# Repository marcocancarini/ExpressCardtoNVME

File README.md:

# ExpressCard → M.2 NVMe for the ThinkPad X230

An adapter that lets you use an **M.2 NVMe 2230 or 2242** SSD (M-key or B+M-key) in the **ExpressCard/54** slot
of a ThinkPad X230 (and in general in any ExpressCard slot with PCIe). It is a bare board, with no shell, that slides
straight into the slot. It is 70 mm long, like "short" ExpressCards: it sits flush with the slot instead of sticking out.

> **Status:** design complete and DRC-clean, **not yet manufactured or tested on hardware**.
> Before ordering, follow the *Checks before ordering* section of the [guide](GUIDE.md).

## Variants

| Variant | Form factor | USB | Notes |
|---|---|---|---|
| `EC2M2_34` | ExpressCard/34 (34 × 70 mm) | no | fits /34 and /54 slots |
| `EC2M2_34_USB5V` | ExpressCard/34 | yes, 5 V | USB pads on the left side, next to the M.2 |
| `EC2M2_54` | ExpressCard/54 (L-shaped, 54 × 70 mm) | no | more stable in a /54 slot |
| `EC2M2_54_USB5V` | ExpressCard/54 | yes, 5 V | USB pads + cut-out to house a small USB receiver |

| 34 mm | 34 mm + USB | 54 mm | 54 mm + USB |
|---|---|---|---|
|  |  |  |  |

The renders show the bare board only (outline, copper, silkscreen): the components have no 3D models here.

## Features

- **PCIe x1** from the ExpressCard slot to the M.2 connector (M-key, low-profile 2.3 mm: **single-sided SSDs only**); differential pairs at **~86 Ω**
  (computed with an included 2D field solver, `gen/impedance.py`).
- **Screw mounting** for the SSD (**single-sided only**): two M2 SMT nuts (H 1.0 mm) on the bottom side at the 2230 and 2242
  positions (hand-soldered, optional: without them the SSD is held with kapton tape).
- SSD **activity LED** and an optional **CLKREQ#→GND jumper** for SSDs that are not detected.
- **USB versions:** the slot's USB 2.0 port is brought out to pads, with a **3.3 → 5 V boost** (TPS61240, 200 mA guaranteed)
  because the ExpressCard slot does not provide 5 V. The power block sits in the free strip to the left of the SSD. A **separate 3.3 V pad** (3V3) is for 3.3 V devices
  or measurements; it is placed away from the 5V pad so the two cannot be confused.
- 2 layers, **0.6 mm** thick (required by the ExpressCard connector), JLCPCB-compatible rules; BOM with LCSC part numbers and assembly-ready files.
- ExpressCard connector footprint and board outline (arms into the connector rails) taken from the FCI **10030570** drawing (rev M).
- On the back: a small **QR code** linking to this repository.
- **3D-printable case** for transport and storage (see below).

## Printable case

In the slot the board must be used **bare**: the ExpressCard connector housing already takes the whole 5.0 mm module
thickness, and the board + SSD fit inside that height, so there is no room for a shell. The case is for carrying and storing it with the SSD installed: the board slides in
from the open side, two small bumps hold it in place and the notches let you grab it.

- Ready-made STLs: `out/enclosure/EC2M2_34_case.stl` (38 × 72 × 8.4 mm) and `EC2M2_54_case.stl` (58 × 72 × 8.4 mm).
- Editable source: `out/enclosure/enclosure.scad` (OpenSCAD), or the parameters in `gen/enclosure.py`.
- Print it **standing on its open side**: no supports or long bridges. PLA or PETG, 0.2 mm layers, 3 perimeters.

## Repository contents

```
gen/                 generator and tools
  gen_board.py       builds the PCB of one variant (KiCad 10 Python API)
  build.sh           generates the 4 variants + DRC
  fab.sh             Gerbers, drill, CPL, renders, 1:1 PDF, JLCPCB files
  render.sh          3D renders into docs/img
  check_nets.py      checks the netlist against the expected mapping
  impedance.py       differential pair impedance calculation (requires scipy)
  jlc_search.py      LCSC/JLC part number search
  jlc_files.py       JLC-format BOM/CPL, LCSC cart, component cost estimate
  enclosure.py       3D-printable case (STL + OpenSCAD)
out/<variant>/       KiCad project (.kicad_pcb/.kicad_pro/.kicad_dru), BOM, footprint library
  fab/               Gerbers, drill, CPL, 1:1 PDF, quick renders
  jlcpcb/            Gerber zip, BOM and CPL for JLCPCB, LCSC cart (hand assembly), cost estimate
out/enclosure/       case STLs and OpenSCAD source
docs/img/            renders
GUIDE.md             checks, ordering, assembly, first boot
HANDOFF.md           design notes: pinout, choices, calculations
```

## Regenerating the files

You need KiCad 10 with the footprint libraries (`kicad-library`, or `KICAD_FPLIB=<footprints dir>`) and Python 3.

```sh
gen/build.sh        # generates the 4 variants and runs the DRC
gen/fab.sh          # production and JLCPCB files
gen/render.sh       # renders (also needs kicad-library-3d)
```

For impedance and the case: `python3 -m venv gen/.venv && gen/.venv/bin/pip install scipy manifold3d trimesh matplotlib`.
Case: `gen/.venv/bin/python gen/enclosure.py`. Impedance:
`gen/.venv/bin/python gen/impedance.py 0.4,0.15,0.25,0.53` (width, spacing between traces, distance to GND,
dielectric height, in mm; 0.53 for the 0.6 mm board).

## Indicative cost

Only the components assembled by JLCPCB (API prices, November 2026): about **$5** for 5 boards without USB, **$11** with USB,
plus the PCB, assembly setup and shipping. Details in `out/<variant>/jlcpcb/<variant>_estimate.md`.
The ExpressCard connector is not available from LCSC: it must be bought separately and soldered by hand, like the
two M2 nuts on the bottom side.

## Known issues and sourcing notes

- **J1 (ExpressCard connector) sourcing.** Not on LCSC. The footprint follows the FCI/Amphenol **10030570**
  drawing (rev M): 26 pos, 1 row, 1.0 mm pitch, SMT, housing 34 × 5 × 11 mm. The connector expects a **0.6 mm**
  board, which it holds at mid-height by two arms in its rails. The last digit of the part number sets the height
  of the board inside the 5 mm module ("solder tail offset"). Only **10030570-6xxxLF** (+1.15) leaves enough room
  (~3.15 mm) above the board for the SSD. The common **10030570-2112LF** (+0.30, RS 615-9467, Digi-Key 1001395) leaves only ~2.3 mm, so
  the SSD would not fit in the slot. A **donor ExpressCard** connector (e.g. from USB 3.0 ExpressCard/34 cards)
  has an unknown offset: measure it before use. Always check the real connector against
  `fab/<variant>_print_1to1.pdf` printed at 100 % (pads, pin 1, arms).
- **SSD height.** The M.2 connector is the low-profile HOAUC HYCW25M-05NGFF-230B (2.3H): the SSD top sits ≤ 2.75 mm
  above the board. Only **single-sided** 2230/2242 SSDs (no components on the underside) fit.
- **Netclass diff-pair defaults** in the generated `.kicad_pro` (width 0.3 / gap 0.2) do not match the actual
  pair geometry (width 0.4 / gap 0.15); the tracks have explicit widths, so this is cosmetic only.
- **Height figures** (tail offset, room above/below the board) were read off the connector drawing's section view,
  not from printed dimensions: treat the first boards as test pieces.
- **Known design limits** (details in HANDOFF.md): REFCLK runs on B.Cu over the GND plane (impedance not
  controlled there), M.2 pins 51 and 67 left NC, no series AC capacitors on the PCIe pairs (they are on the
  host and the SSD).
- **Verification status:** DRC clean and `check_nets.py` OK on all 4 variants; regenerating with
  `gen/build.sh` reproduces the committed files (modulo UUIDs/timestamps). Still **not manufactured or tested
  on hardware** — follow the checks in GUIDE.md before ordering.

## License

This project (hardware design, documentation and scripts) is released under the
[Creative Commons Attribution-NonCommercial-ShareAlike 4.0 International](https://creativecommons.org/licenses/by-nc-sa/4.0/)
license (CC BY-NC-SA 4.0). You may build, modify and share it for **non-commercial** purposes, crediting the author and
releasing derivative works under the same license. Selling boards or derivatives requires permission from the author.
See [LICENSE](LICENSE).

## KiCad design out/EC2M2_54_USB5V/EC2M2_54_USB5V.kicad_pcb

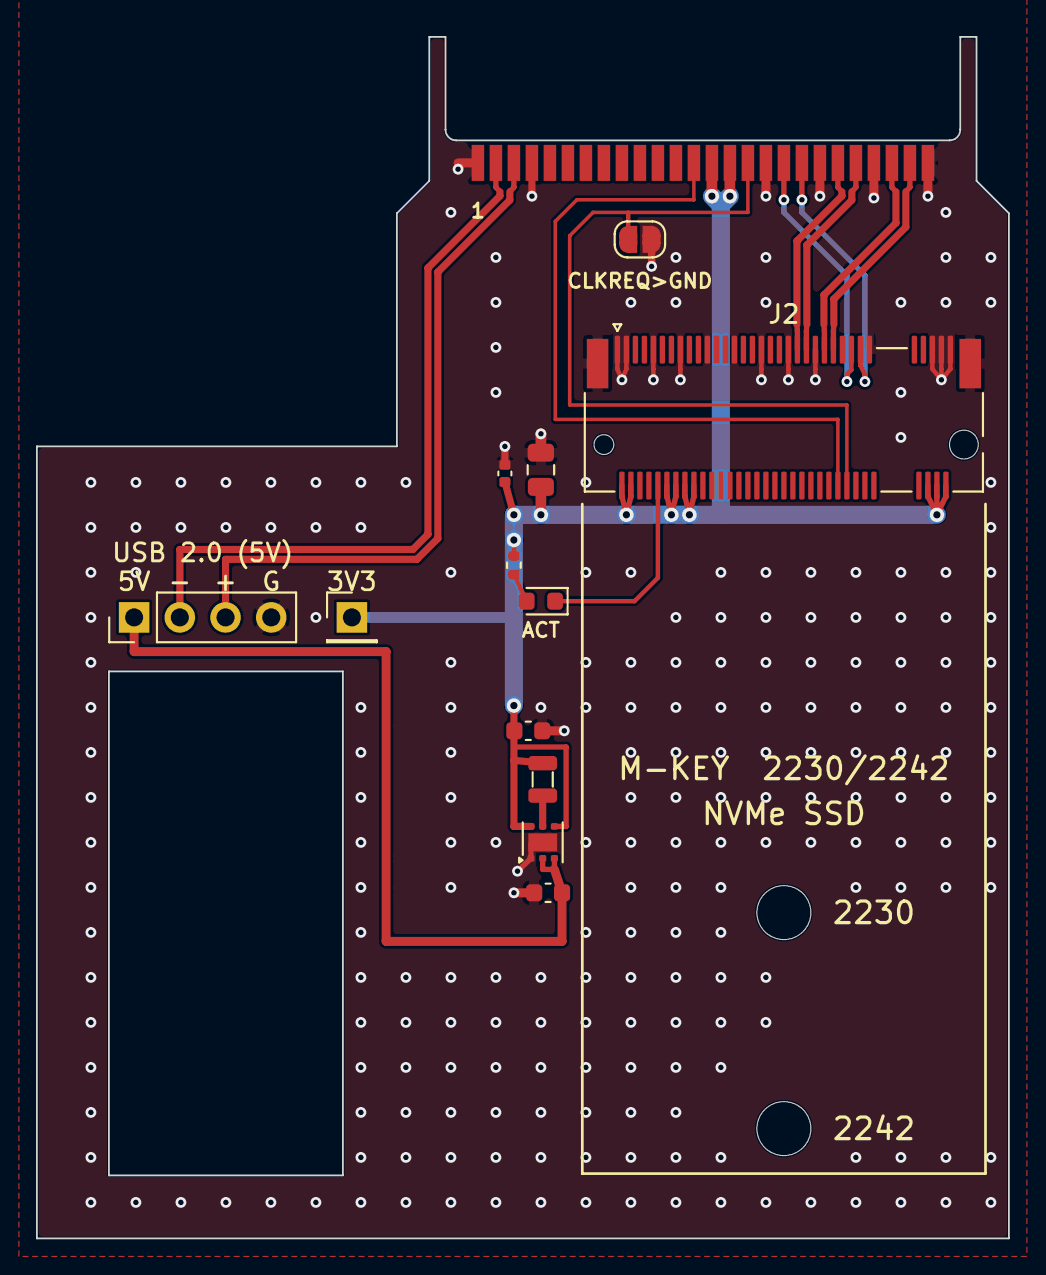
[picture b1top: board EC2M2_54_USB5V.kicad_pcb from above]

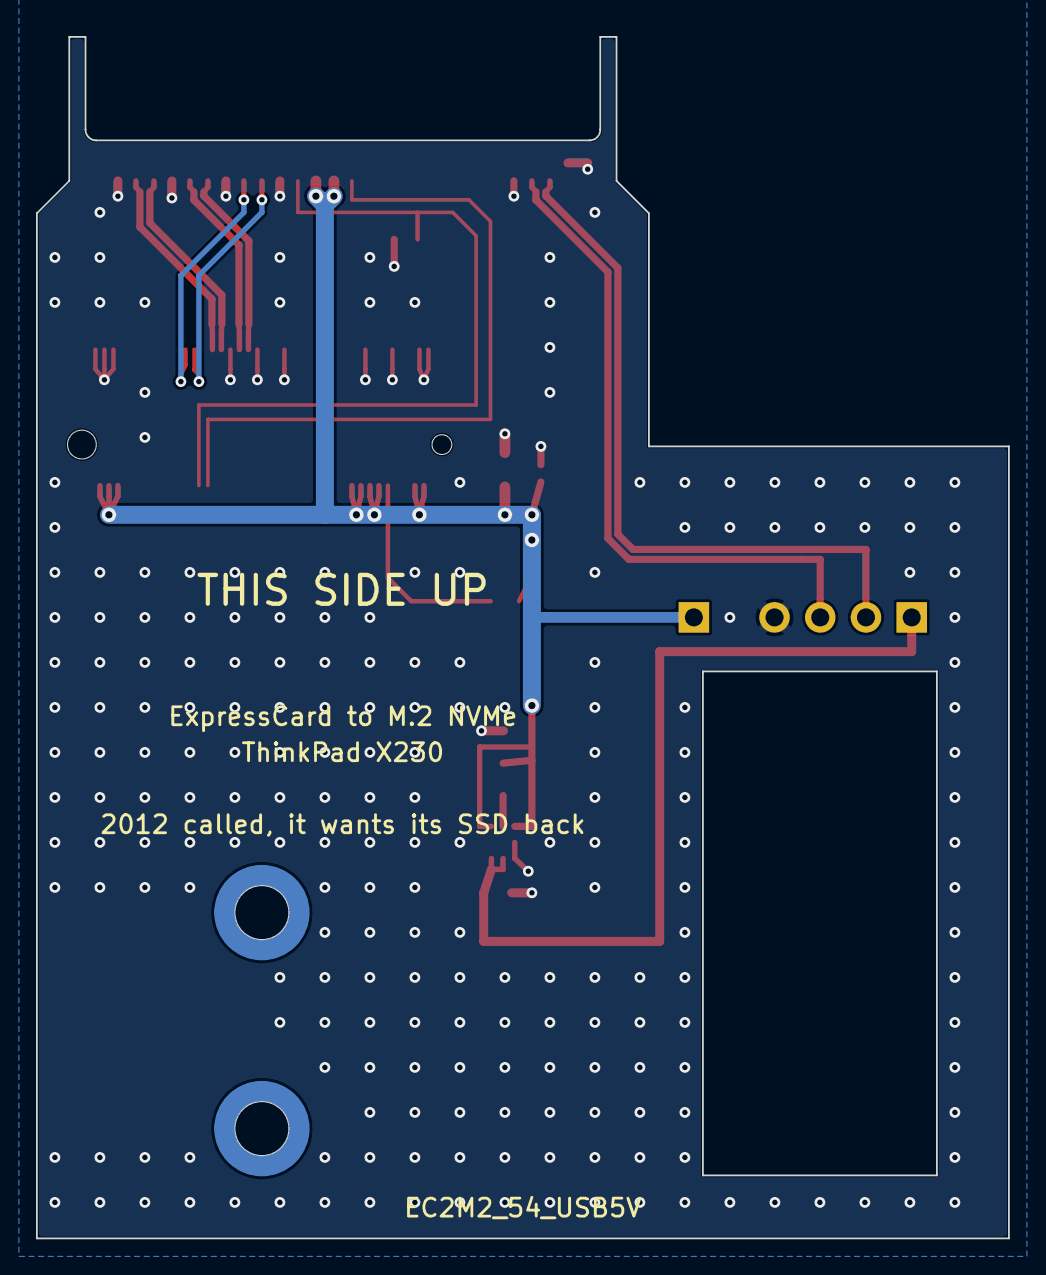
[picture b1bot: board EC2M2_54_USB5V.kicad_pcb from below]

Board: 2 copper layers, 54.0 x 66.8 mm, 15 parts (2 on the bottom side), 16 nets.

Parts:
C1: 22uF; C_0805_2012Metric
C2: 100nF; C_0402_1005Metric
C3, C4: 10uF; C_0603_1608Metric
D1: LED red; LED_0603_1608Metric
H1, H2: M2 SMT nut H1.0; Mounting_Wuerth_WA-SMSI-M2_H1mm_9774010243
J1: ExpressCard 26P; ExpressCard_Module_1x26_P1.0mm
J2: M.2 M-key H2.3; TE_M.2_M_2x38-1MP_P0.5mm
J3: USB pads; PinHeader_1x04_P2.54mm_Vertical
J4: 3V3 pad; PinHeader_1x01_P2.54mm_Vertical
JP1: CLKREQ-GND; SolderJumper-2_P1.3mm_Open_RoundedPad1.0x1.5mm
L1: 1uH; L_TDK_MLP2016
R1: 470; R_0402_1005Metric
U1: TPS61240DRV; WSON-6-1EP_2x2mm_P0.65mm_EP1x1.6mm

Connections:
+3V3: C1.1, C2.1, C3.1, J1.14, J1.15, J2.2, J2.4, J2.12, J2.14, J2.16, J2.18, J2.70, J2.72, J2.74, J4.1, L1.2, R1.2, U1.4, U1.6
+5V: C4.1, J3.1, U1.2, U1.3
CLKREQ#: J1.16, J2.52, JP1.1
GND: C1.2, C2.2, C3.2, C4.2, J1.1, J1.4, J1.17, J1.20, J1.23, J1.26, J2.1, J2.3, J2.9, J2.15, J2.21, J2.27, J2.33, J2.39, J2.45, J2.57, J2.71, J2.73, J2.75, J2.MP, J3.4, JP1.2, U1.1, U1.7
LED#: D1.1, J2.10
LED_A: D1.2, R1.1
PERST#: J1.13, J2.50
PERn0: J1.21, J2.41
PERp0: J1.22, J2.43
PETn0: J1.24, J2.47
PETp0: J1.25, J2.49
REFCLK+: J1.19, J2.55
REFCLK-: J1.18, J2.53
SW: L1.1, U1.5
USB_D+: J1.3, J3.3
USB_D-: J1.2, J3.2

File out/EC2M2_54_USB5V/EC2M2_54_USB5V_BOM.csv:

Comment,Designator,Footprint,LCSC,Note
22uF,C1,C_0805_2012Metric,C45783,22uF 25V X5R 0805
100nF,C2,C_0402_1005Metric,C1525,100nF 0402
10uF,C3,C_0603_1608Metric,C19702,10uF 10V X5R 0603
10uF,C4,C_0603_1608Metric,C19702,10uF 10V X5R 0603
LED red,D1,LED_0603_1608Metric,C2286,LED red 0603 (Vf~2V)
M2 SMT nut H1.0,H1,Mounting_Wuerth_WA-SMSI-M2_H1mm_9774010243,C5360192,"Wurth 9774010243R M2 SMT nut H1.0 (alt. Sinhoo SMTSO2010CTJ C2916319, verify land)"
M2 SMT nut H1.0,H2,Mounting_Wuerth_WA-SMSI-M2_H1mm_9774010243,C5360192,"Wurth 9774010243R M2 SMT nut H1.0 (alt. Sinhoo SMTSO2010CTJ C2916319, verify land)"
ExpressCard 26P,J1,ExpressCard_Module_1x26_P1.0mm,,"ExpressCard 26P module side SMT, 1.0 pitch (e.g. Amphenol 10030570-2113LF, JAE PX10) - VERIFY footprint"
M.2 M-key H3.2,J2,TE_M.2_M_2x38-1MP_P0.5mm,C52766481,M.2 M-key H3.2 Minlenda MLD-NGFF-M-3.2H (land pattern = TE 2199230)
USB pads,J3,PinHeader_1x04_P2.54mm_Vertical,,pads for soldered wires (no header: it would not fit in the slot)
3V3 pad,J4,PinHeader_1x01_P2.54mm_Vertical,,
CLKREQ-GND,JP1,SolderJumper-2_P1.3mm_Open_RoundedPad1.0x1.5mm,,solder jumper (open)
1uH,L1,L_0805_2012Metric,C76793,1uH 0805 1.4A 90mohm MLP2016S1R0MT0S1
470,R1,R_0402_1005Metric,C25117,470R 0402
TPS61240DRV,U1,WSON-6-1EP_2x2mm_P0.65mm_EP1x1.6mm,C59567,TPS61240DRVR
